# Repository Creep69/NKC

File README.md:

# NKC
## Neuauflage des NDR KLEIN COMPUTER

Hier sollen Hardware- und Softwareprojekte zum NDR Klein Computer ihren Platz finden.

Weitere Mitstreiter sind herzlich willkommen!

Links:

www.nkc-wiki.de

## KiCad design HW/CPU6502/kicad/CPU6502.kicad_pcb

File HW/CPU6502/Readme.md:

NKC CPU6502 v0.1 Prototyp 3.1.2019

Prototyp einer 65(c)02 CPU Platine für das NDR Klein Computersystem

Entwickelt von Rene Vetter mit Unterstützung von Jens Mewes basierend auf den Erläuterungen zu einer 6502-Karte am Z80-BUS:

https://ancientcomputing.blogspot.com/2017/05/a-6502-cpu-for-rc2014-part-1.html

History:

V0.1: 3.1.2019 RV
Erster Prototyp

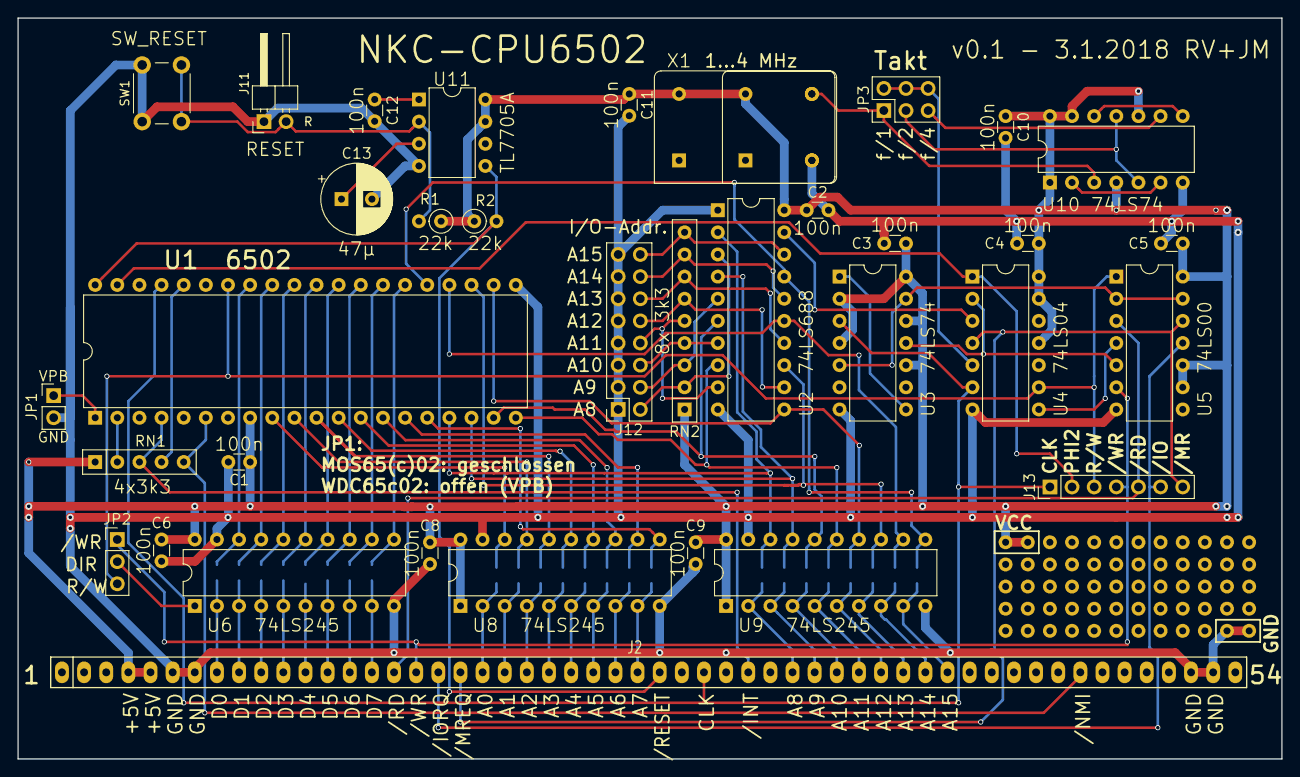
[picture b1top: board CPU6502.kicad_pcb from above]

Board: 2 copper layers, 145.0 x 85.0 mm, 39 parts (0 on the bottom side), 86 nets.

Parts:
C1, C2, C3, C4, C5, C6, C8, C9, C10, C11, C12: 100n; C_Disc_D3.0mm_W1.6mm_P2.50mm
C13: 47µ; CP_Radial_D8.0mm_P3.50mm
J2: NKC-BUS-full
J6: Conn_D; Lötbrücke_8_2
J8: Conn_A1; Lötbrücke_8_2
J9: Conn_A2; Lötbrücke_8_2
J11: RESET; PinHeader_1x02_P2.54mm_Horizontal
J12: Conn_IO_Address; PinHeader_2x08_P2.54mm_Vertical-gespiegelt
J13: Conn_Proto; PinHeader_1x07_P2.54mm_Vertical
JP1: 6502/65c02; PinHeader_1x02_P2.54mm_Vertical
JP2: /W_R/W; PinHeader_1x03_P2.54mm_Vertical
JP3: Conn_CLK; PinHeader_2x03_P2.54mm_Vertical
R1, R2: 22k; R_Axial_DIN0207_L6.3mm_D2.5mm_P2.54mm_Vertical
RN1: 4x3k3; R_Array_SIP5
RN2: 8x 3k3; R_Array_SIP9
SW1: SW_RESET; SW_PUSH_6mm
U1: 6502; DIP-40_W15.24mm
U2: 74LS688; DIP-20_W7.62mm
U3, U10: 74LS74; DIP-14_W7.62mm
U4: 74LS04; DIP-14_W7.62mm
U5: 74LS00; DIP-14_W7.62mm
U6, U8, U9: 74LS245; DIP-20_W7.62mm
U11: TL7705A; DIP-8_W7.62mm
X1: ACO-4MHz; Oscillator_DIP-14
X2: CXO_4MHz; Oscillator_DIP-8

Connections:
/-INT: J2.32, RN1.3, U1.4
/-IORQ: J2.18, J13.6, U5.11
/-MREQ: J2.19, J13.7, U4.4, U5.12
/-NMI: J2.47, RN1.5, U1.6
/-PHI2: U3.11, U4.2, U5.5
/-RD: J2.16, J13.5, U5.3
/-RESET: J2.28, R2.2, U1.40, U11.5
/-WR: J2.17, J13.4, JP2.1, U5.6
/A0: J8.1b, U1.9, U8.18
/A1: J8.2b, U1.10, U8.17
/A2: J8.3b, U1.11, U8.16
/A3: J8.4b, U1.12, U8.15
/A4: J8.5b, U1.13, U8.14
/A5: J8.6b, U1.14, U8.13
/A6: J8.7b, U1.15, U8.12
/A7: J8.8b, U1.16, U8.11
/A8: J9.1b, U1.17, U2.2, U9.18
/A9: J9.2b, U1.18, U2.4, U9.17
/A10: J9.3b, U1.19, U2.6, U9.16
/A11: J9.4b, U1.20, U2.8, U9.15
/A12: J9.5b, U1.22, U2.11, U9.14
/A13: J9.6b, U1.23, U2.13, U9.13
/A14: J9.7b, U1.24, U2.15, U9.12
/A15: J9.8b, U1.25, U2.17, U9.11
/BE: RN1.4, U1.36
/CLK: J2.30, J13.1, U1.37, U3.3, U4.6
/D0: J6.1b, U1.33, U6.18
/D1: J6.2b, U1.32, U6.17
/D2: J6.3b, U1.31, U6.16
/D3: J6.4b, U1.30, U6.15
/D4: J6.5b, U1.29, U6.14
/D5: J6.6b, U1.28, U6.13
/D6: J6.7b, U1.27, U6.12
/D7: J6.8b, U1.26, U6.11
/NKC_A0: J2.20, J8.1a, U8.2
/NKC_A1: J2.21, J8.2a, U8.3
/NKC_A2: J2.22, J8.3a, U8.4
/NKC_A3: J2.23, J8.4a, U8.5
/NKC_A4: J2.24, J8.5a, U8.6
/NKC_A5: J2.25, J8.6a, U8.7
/NKC_A6: J2.26, J8.7a, U8.8
/NKC_A7: J2.27, J8.8a, U8.9
/NKC_A8: J2.34, J9.1a, U9.2
/NKC_A9: J2.35, J9.2a, U9.3
/NKC_A10: J2.36, J9.3a, U9.4
/NKC_A11: J2.37, J9.4a, U9.5
/NKC_A12: J2.38, J9.5a, U9.6
/NKC_A13: J2.39, J9.6a, U9.7
/NKC_A14: J2.40, J9.7a, U9.8
/NKC_A15: J2.41, J9.8a, U9.9
/NKC_D0: J2.8, J6.1a, U6.2
/NKC_D1: J2.9, J6.2a, U6.3
/NKC_D2: J2.10, J6.3a, U6.4
/NKC_D3: J2.11, J6.4a, U6.5
/NKC_D4: J2.12, J6.5a, U6.6
/NKC_D5: J2.13, J6.6a, U6.7
/NKC_D6: J2.14, J6.7a, U6.8
/NKC_D7: J2.15, J6.8a, U6.9
/PHI2: J13.2, U1.39, U4.1
/R-W: J13.3, JP2.3, U1.34, U4.9, U5.1
/RDY: RN1.2, U1.2
GND: C1.2, C2.2, C3.2, C4.2, C5.2, C6.2, C8.2, C9.2, C10.2, C11.2, C12.2, C13.2, J2.6, J2.7, J2.52, J2.53, J11.1, J12.1, J12.3, J12.5, J12.7, J12.9, J12.11, J12.13, J12.15, JP1.2, SW1.1, U1.21, U2.1, U2.10, U3.7, U4.7, U5.7, U6.10, U6.19, U8.10, U8.19, U9.10, U9.19, U10.7, U11.4, X1.7, X2.4
unnamed: C12.1, U11.1
unnamed: C13.1, U11.3
unnamed: J11.2, R1.2, SW1.2, U11.2
unnamed: J12.2, RN2.2, U2.3
unnamed: J12.4, RN2.3, U2.5
unnamed: J12.6, RN2.4, U2.7
unnamed: J12.8, RN2.5, U2.9
unnamed: J12.10, RN2.6, U2.12
unnamed: J12.12, RN2.7, U2.14
unnamed: J12.14, RN2.8, U2.16
unnamed: J12.16, RN2.9, U2.18
unnamed: JP1.1, U1.1
unnamed: JP2.2, U6.1
unnamed: JP3.1, U10.3, X1.8, X2.5
unnamed: JP3.2, JP3.4, JP3.6, U4.5
unnamed: JP3.3, U10.5, U10.11
unnamed: JP3.5, U10.9
unnamed: U2.19, U4.3
unnamed: U3.1, U3.8
unnamed: U3.5, U3.13, U5.2, U5.13
unnamed: U4.8, U5.4
unnamed: U10.2, U10.6
unnamed: U10.8, U10.12
VCC: C1.1, C2.1, C3.1, C4.1, C5.1, C6.1, C8.1, C9.1, C10.1, C11.1, J2.4, J2.5, R1.1, R2.1, RN1.1, RN2.1, U1.8, U2.20, U3.2, U3.4, U3.10, U3.12, U3.14, U4.11, U4.13, U4.14, U5.9, U5.10, U5.14, U6.20, U8.1, U8.20, U9.1, U9.20, U10.1, U10.4, U10.10, U10.13, U10.14, U11.7, U11.8, X1.14, X2.8

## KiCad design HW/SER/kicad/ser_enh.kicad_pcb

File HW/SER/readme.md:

verbesserte Neuauflage der SER des NKC - serielle I/O-Platine

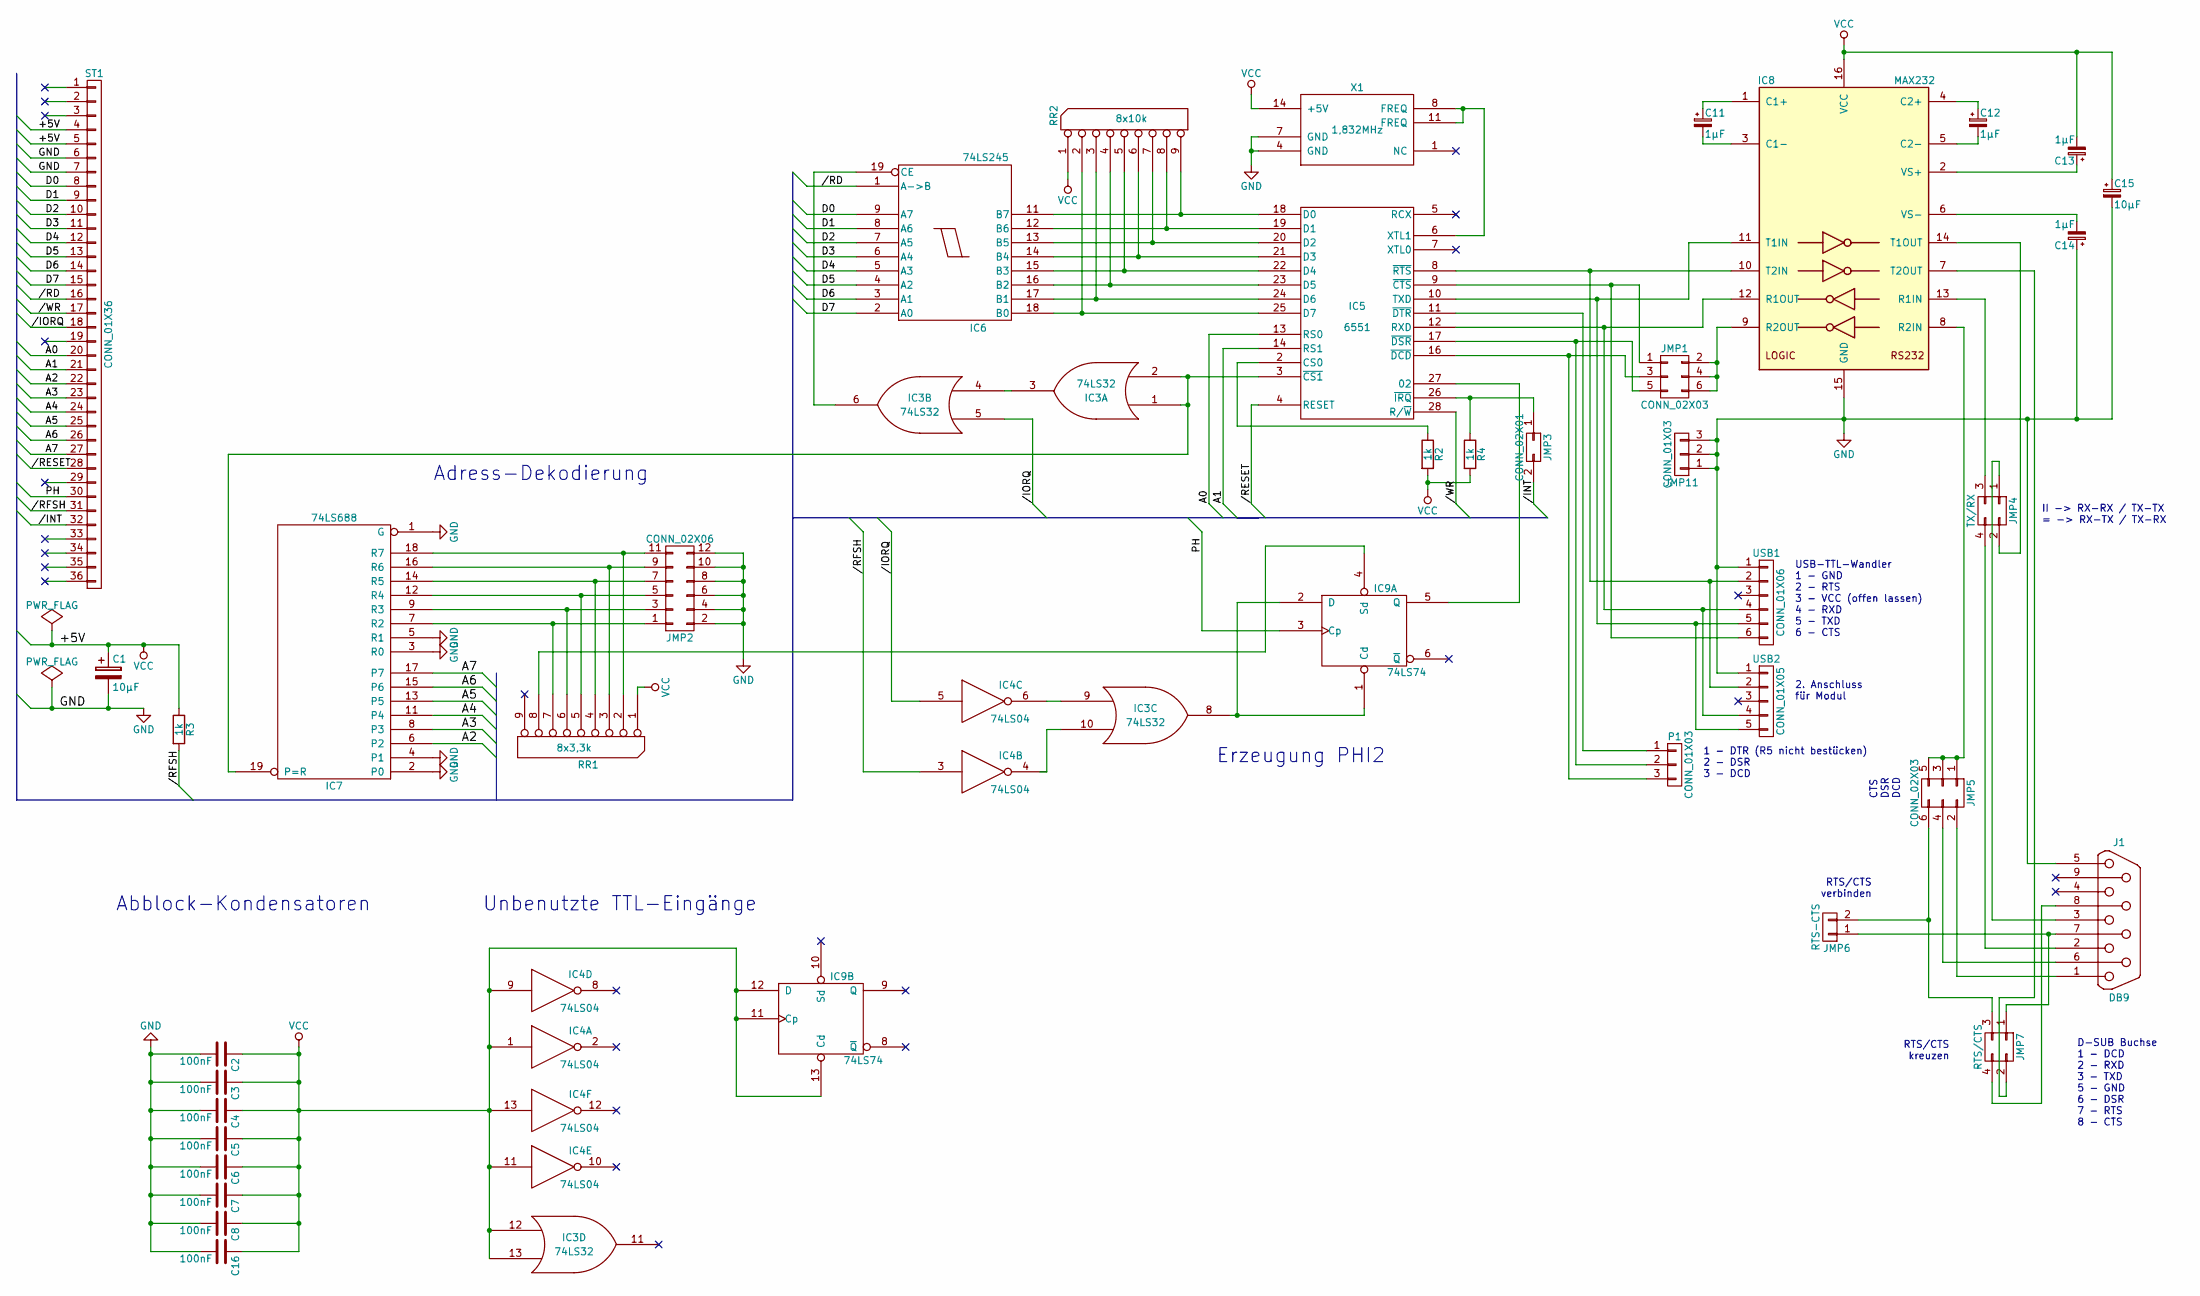
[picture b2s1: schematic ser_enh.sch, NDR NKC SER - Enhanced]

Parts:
C1: 10µF; C_Radial_D5_L6_P2.5
C2, C3, C4, C5, C6, C7, C8, C16: 100nF; C_Disc_D3_P2.5
C11, C12, C13, C14: 1µF; C_Radial_D5_L11_P2
C15: 10µF; C_Radial_D5_L11_P2
IC3: 74LS32; DIP-14
IC4: 74LS04; DIP-14
IC5: 6551; DIP-28_Breit
IC6: 74LS245; DIP-20
IC7: 74LS688; DIP-20
IC8: MAX232; DIP-16
IC9: 74LS74; DIP-14
J1: DB9; DB9MC_EU
JMP1, JMP5: CONN_02X03; Pin_Header_Straight_2x03
JMP2: CONN_02X06; Pin_Header_Straight_2x06
JMP3: CONN_02X01; Pin_Header_Straight_2x01
JMP4: TX/RX; Pin_Header_Straight_2x02
JMP6: RTS-CTS; Pin_Header_Straight_1x02
JMP7: RTS/CTS; Pin_Header_Straight_2x02
JMP11: CONN_01X03; Pin_Header_Straight_1x03
P1: CONN_01X03; Pin_Header_Straight_1x03
R2, R3, R4: 1k; Resistor_Horizontal_RM10mm
RR1: 8x3,3k; Resistor_Array_SIP8
RR2: 8x10k; Resistor_Array_SIP8
ST1: CONN_01X36; NKC_BUS_36_Names
USB1: CONN_01X06; Pin_Header_Straight_1x06
USB2: CONN_01X05; Pin_Header_Straight_1x05
X1: 1,832MHz; OSZI_6pin

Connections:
//INT: JMP3.2, ST1.32
//IORQ: IC3.5, IC4.5, ST1.18
//RD: IC6.1 (A->B), ST1.16
//RESET: IC5.4 (RESET), ST1.28
//RFSH: IC4.3, R3.2, ST1.31
//WR: IC5.28 (R/~W), ST1.17
/A0: IC5.13 (RS0), ST1.20
/A1: IC5.14 (RS1), ST1.21
/A2: IC7.6 (P2), ST1.22
/A3: IC7.8 (P3), ST1.23
/A4: IC7.11 (P4), ST1.24
/A5: IC7.13 (P5), ST1.25
/A6: IC7.15 (P6), ST1.26
/A7: IC7.17 (P7), ST1.27
/D0: IC6.9 (A7), ST1.8
/D1: IC6.8 (A6), ST1.9
/D2: IC6.7 (A5), ST1.10
/D3: IC6.6 (A4), ST1.11
/D4: IC6.5 (A3), ST1.12
/D5: IC6.4 (A2), ST1.13
/D6: IC6.3 (A1), ST1.14
/D7: IC6.2 (A0), ST1.15
/PH: IC9.3 (Cp), ST1.30
GND: C1.2, C2.2, C3.2, C4.2, C5.2, C6.2, C7.2, C8.2, C14.1, C15.2, C16.2, IC3.7 (GND), IC4.7 (GND), IC5.1 (GND), IC6.10 (GND), IC7.1 (G), IC7.2 (P0), IC7.3 (R0), IC7.4 (P1), IC7.5 (R1), IC7.10 (GND), IC8.15 (GND), IC9.7 (GND), J1.5, JMP2.2, JMP2.4, JMP2.6, JMP2.8, JMP2.10, JMP2.12, JMP11.1, JMP11.2, JMP11.3, ST1.6, ST1.7, USB1.1, USB2.1, X1.4 (GND), X1.7 (GND)
unnamed: C11.1, IC8.1 (C1+)
unnamed: C11.2, IC8.3 (C1-)
unnamed: C12.1, IC8.4 (C2+)
unnamed: C12.2, IC8.5 (C2-)
unnamed: C13.1, IC8.2 (VS+)
unnamed: C14.2, IC8.6 (VS-)
unnamed: IC3.1, IC3.2, IC5.3 (~CS1), IC7.19 (P=R)
unnamed: IC3.3, IC3.4
unnamed: IC3.6, IC6.19 (CE)
unnamed: IC3.8, IC9.1 (Cd), IC9.2 (D)
unnamed: IC3.9, IC4.6
unnamed: IC3.10, IC4.4
unnamed: IC5.2 (CS0), R2.1
unnamed: IC5.6 (XTL1), X1.8 (FREQ), X1.11 (FREQ)
unnamed: IC5.8 (~RTS), IC8.10 (T2IN), USB1.2, USB2.2
unnamed: IC5.9 (~CTS), JMP1.1, USB1.6
unnamed: IC5.10 (TXD), IC8.11 (T1IN), USB1.5, USB2.5
unnamed 41: IC5.11 (~DTR), P1.1; also elsewhere on the board
unnamed: IC5.12 (RXD), IC8.12 (R1OUT), USB1.4, USB2.4
unnamed: IC5.16 (~DCD), JMP1.3, P1.3
unnamed: IC5.17 (~DSR), JMP1.5, P1.2
unnamed: IC5.18 (D0), IC6.11 (B7), RR2.9
unnamed: IC5.19 (D1), IC6.12 (B6), RR2.8
unnamed: IC5.20 (D2), IC6.13 (B5), RR2.7
unnamed: IC5.21 (D3), IC6.14 (B4), RR2.6
unnamed: IC5.22 (D4), IC6.15 (B3), RR2.5
unnamed: IC5.23 (D5), IC6.16 (B2), RR2.4
unnamed: IC5.24 (D6), IC6.17 (B1), RR2.3
unnamed: IC5.25 (D7), IC6.18 (B0), RR2.2
unnamed: IC5.26 (~IRQ), JMP3.1, R4.1
unnamed: IC5.27 (02), IC9.5 (Q)
unnamed: IC7.7 (R2), JMP2.1, RR1.7
unnamed: IC7.9 (R3), JMP2.3, RR1.6
unnamed: IC7.12 (R4), JMP2.5, RR1.5
unnamed: IC7.14 (R5), JMP2.7, RR1.4
unnamed: IC7.16 (R6), JMP2.9, RR1.3
unnamed: IC7.18 (R7), JMP2.11, RR1.2
unnamed: IC8.7 (T2OUT), JMP7.2
unnamed: IC8.8 (R2IN), JMP5.1, JMP5.3, JMP5.5
unnamed: IC8.9 (R2OUT), JMP1.2, JMP1.4, JMP1.6
unnamed: IC8.13 (R1IN), JMP4.3
unnamed: IC8.14 (T1OUT), JMP4.2
unnamed: IC9.4 (Sd), RR1.8
unnamed: J1.1, JMP5.2
unnamed: J1.2, JMP4.4
unnamed: J1.3, JMP4.1
unnamed: J1.6, JMP5.4
unnamed: J1.7, JMP6.1, JMP7.1
unnamed: J1.8, JMP7.4
unnamed: JMP5.6, JMP6.2, JMP7.3
VCC: C1.1, C2.1, C3.1, C4.1, C5.1, C6.1, C7.1, C8.1, C13.2, C15.1, C16.1, IC3.12, IC3.13, IC3.14 (VCC), IC4.1, IC4.9, IC4.11, IC4.13, IC4.14 (VCC), IC5.15 (Vcc), IC6.20 (VCC), IC7.20 (VCC), IC8.16 (VCC), IC9.11 (Cp), IC9.12 (D), IC9.13 (Cd), IC9.14 (VCC), R2.2, R3.1, R4.2, RR1.1 (COM), RR2.1 (COM), ST1.4, ST1.5, X1.14 (+5V); also elsewhere on the board

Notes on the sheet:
D-SUB Buchse 1 - DCD 2 - RXD 3 - TXD 5 - GND 6 - DSR 7 - RTS 8 - CTS
USB-TTL-Wandler 1 - GND 2 - RTS 3 - VCC (offen lassen) 4 - RXD 5 - TXD 6 - CTS
1 - DTR (R5 nicht bestücken) 2 - DSR 3 - DCD
Adress-Dekodierung
Erzeugung PHI2
Abblock-Kondensatoren
Unbenutzte TTL-Eingänge
II -> RX-RX / TX-TX = -> RX-TX / TX-RX
CTS DSR DCD
2. Anschluss für Modul
RTS/CTS verbinden
RTS/CTS kreuzen

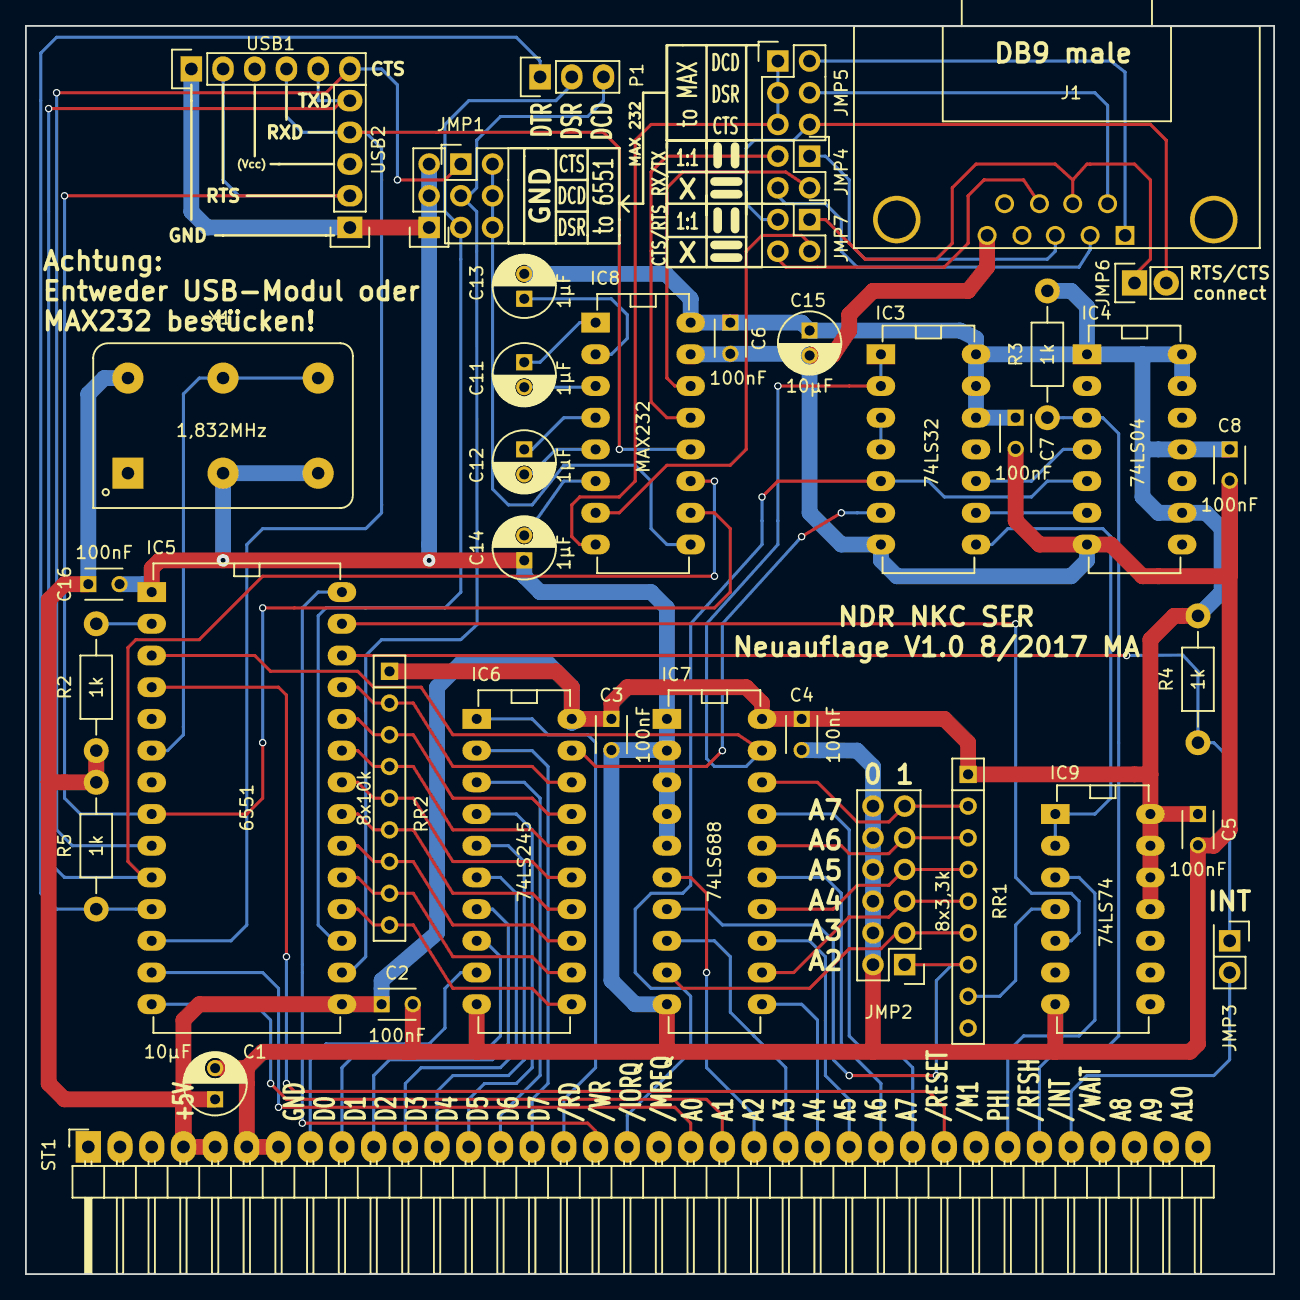
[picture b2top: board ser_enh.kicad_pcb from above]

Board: 2 copper layers, 100.0 x 100.0 mm, 41 parts (0 on the bottom side), 75 nets.

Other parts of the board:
R5: 1k; Resistor_Horizontal_RM10mm

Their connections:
unnamed 41: R5.1; also elsewhere on the board
VCC: R5.2; also elsewhere on the board

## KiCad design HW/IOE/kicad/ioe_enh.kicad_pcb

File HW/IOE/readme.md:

verbesserte Neuauflage der IOE des NKC - parallele I/O-Platine

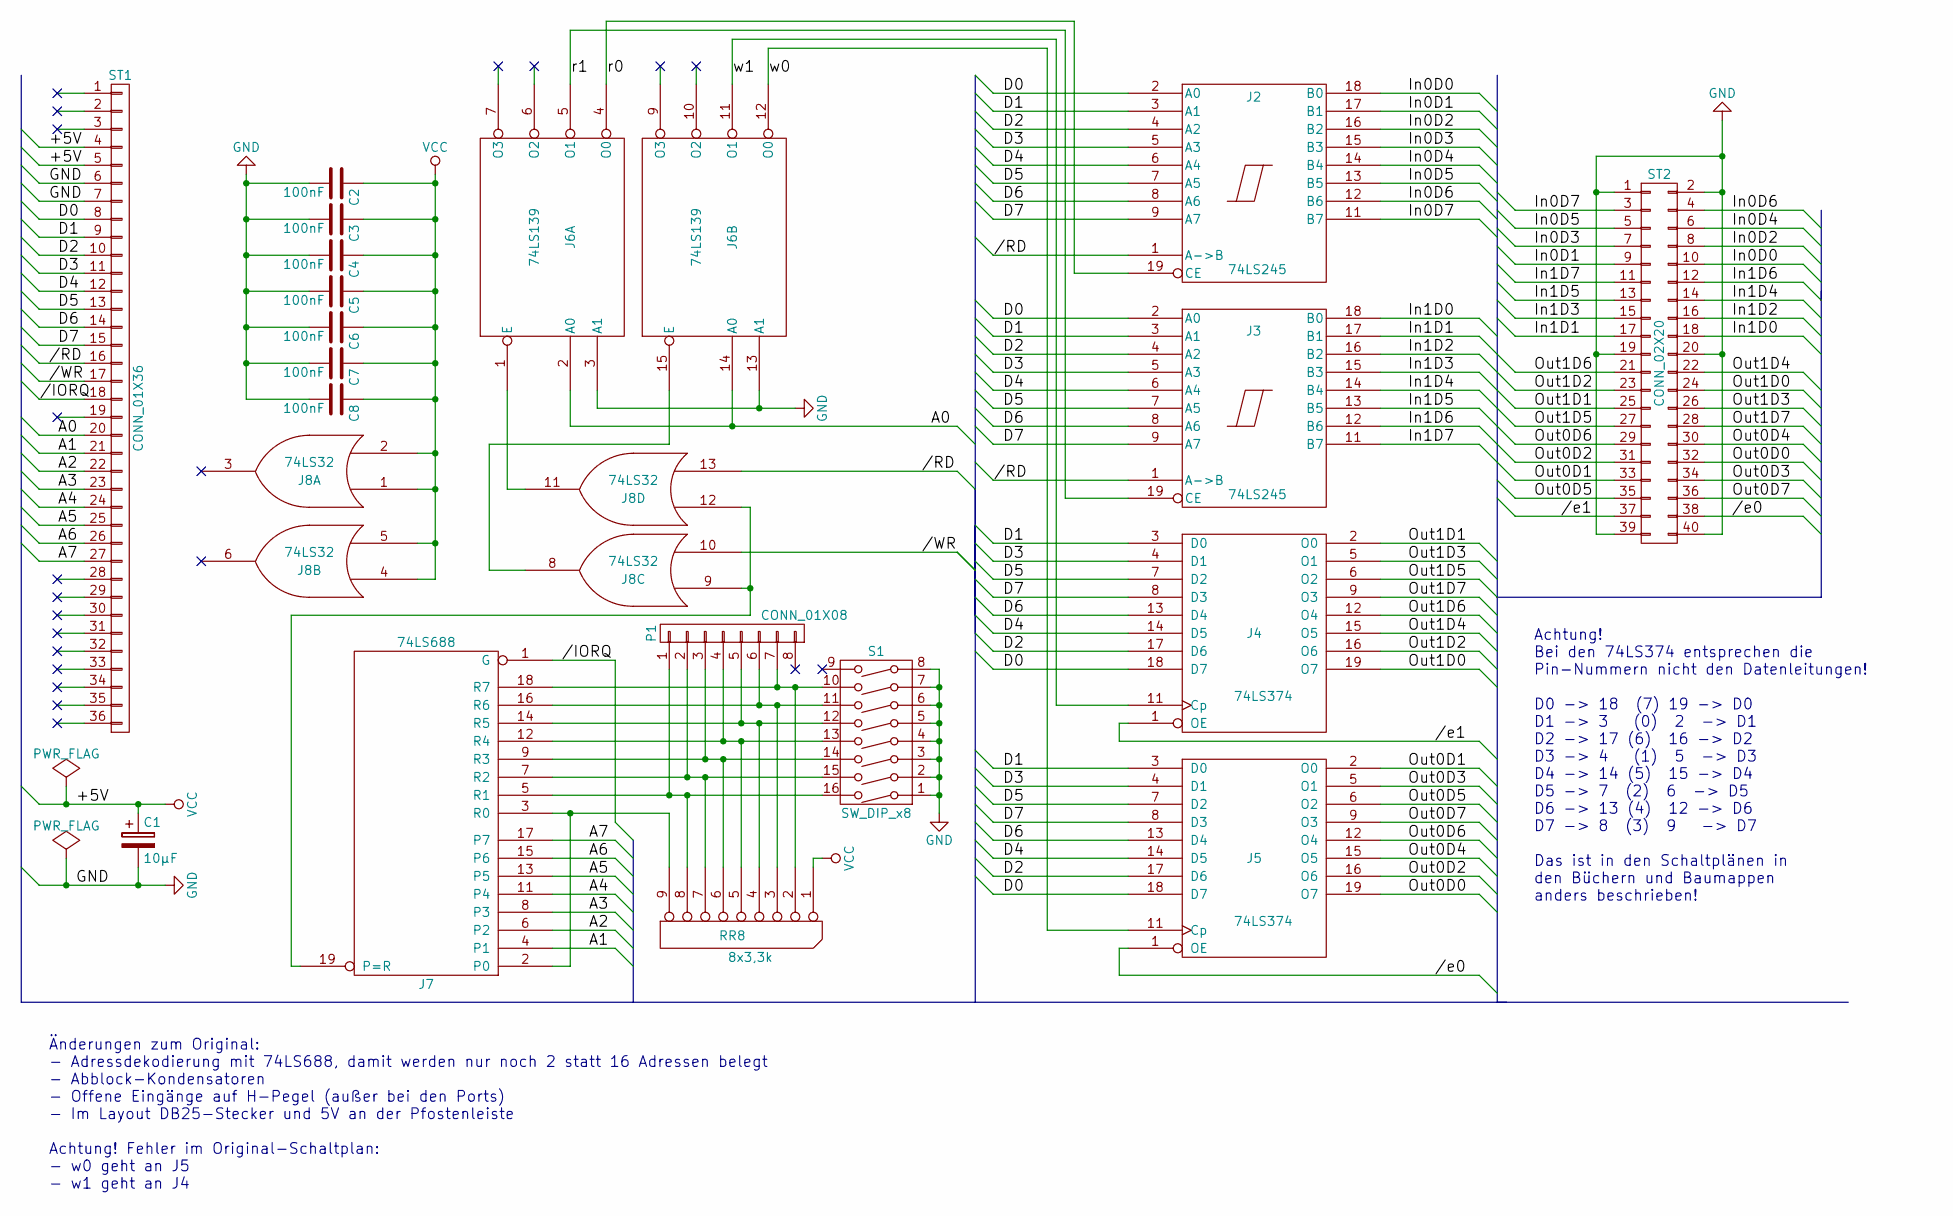
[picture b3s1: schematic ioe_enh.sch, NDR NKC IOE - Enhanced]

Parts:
8x3,3k: RR8; Resistor_Array_SIP8
C1: 10µF; C_Radial_D5_L6_P2.5
C2, C3, C4, C5, C6, C7, C8: 100nF; C_Disc_D3_P2.5
J2, J3: 74LS245; DIP-20_W7.62mm_LongPads
J4, J5: 74LS374; DIP-20_W7.62mm_LongPads
J6: 74LS139; DIP-16_W7.62mm_LongPads
J7: 74LS688; DIP-20_W7.62mm_LongPads
J8: 74LS32; DIP-14_W7.62mm_LongPads
P1: CONN_01X08; Pin_Header_Straight_1x08
S1: SW_DIP_x8; DIP-16_W7.62mm_LongPads
ST1: CONN_01X36; NKC_BUS_36
ST2: CONN_02X20; Pin_Header_Straight_2x20

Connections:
//IORQ: J7.1 (G), ST1.18
//RD: J2.1 (A->B), J3.1 (A->B), J8.13, ST1.16
//WR: J8.10, ST1.17
//e0: J5.1 (OE), ST2.38
//e1: J4.1 (OE), ST2.37
/A0: J6.2 (A0), J6.14 (A0), ST1.20
/A1: J7.4 (P1), ST1.21
/A2: J7.6 (P2), ST1.22
/A3: J7.8 (P3), ST1.23
/A4: J7.11 (P4), ST1.24
/A5: J7.13 (P5), ST1.25
/A6: J7.15 (P6), ST1.26
/A7: J7.17 (P7), ST1.27
/D0: J2.2 (A0), J3.2 (A0), J4.18 (D7), J5.18 (D7), ST1.8
/D1: J2.3 (A1), J3.3 (A1), J4.3 (D0), J5.3 (D0), ST1.9
/D2: J2.4 (A2), J3.4 (A2), J4.17 (D6), J5.17 (D6), ST1.10
/D3: J2.5 (A3), J3.5 (A3), J4.4 (D1), J5.4 (D1), ST1.11
/D4: J2.6 (A4), J3.6 (A4), J4.14 (D5), J5.14 (D5), ST1.12
/D5: J2.7 (A5), J3.7 (A5), J4.7 (D2), J5.7 (D2), ST1.13
/D6: J2.8 (A6), J3.8 (A6), J4.13 (D4), J5.13 (D4), ST1.14
/D7: J2.9 (A7), J3.9 (A7), J4.8 (D3), J5.8 (D3), ST1.15
/In0D0: J2.18 (B0), ST2.10
/In0D1: J2.17 (B1), ST2.9
/In0D2: J2.16 (B2), ST2.8
/In0D3: J2.15 (B3), ST2.7
/In0D4: J2.14 (B4), ST2.6
/In0D5: J2.13 (B5), ST2.5
/In0D6: J2.12 (B6), ST2.4
/In0D7: J2.11 (B7), ST2.3
/In1D0: J3.18 (B0), ST2.18
/In1D1: J3.17 (B1), ST2.17
/In1D2: J3.16 (B2), ST2.16
/In1D3: J3.15 (B3), ST2.15
/In1D4: J3.14 (B4), ST2.14
/In1D5: J3.13 (B5), ST2.13
/In1D6: J3.12 (B6), ST2.12
/In1D7: J3.11 (B7), ST2.11
/Out0D0: J5.19 (O7), ST2.32
/Out0D1: J5.2 (O0), ST2.33
/Out0D2: J5.16 (O6), ST2.31
/Out0D3: J5.5 (O1), ST2.34
/Out0D4: J5.15 (O5), ST2.30
/Out0D5: J5.6 (O2), ST2.35
/Out0D6: J5.12 (O4), ST2.29
/Out0D7: J5.9 (O3), ST2.36
/Out1D0: J4.19 (O7), ST2.24
/Out1D1: J4.2 (O0), ST2.25
/Out1D2: J4.16 (O6), ST2.23
/Out1D3: J4.5 (O1), ST2.26
/Out1D4: J4.15 (O5), ST2.22
/Out1D5: J4.6 (O2), ST2.27
/Out1D6: J4.12 (O4), ST2.21
/Out1D7: J4.9 (O3), ST2.28
/r0: J2.19 (CE), J6.4 (O0)
/r1: J3.19 (CE), J6.5 (O1)
/w0: J5.11 (Cp), J6.12 (O0)
/w1: J4.11 (Cp), J6.11 (O1)
GND: C1.2, C2.2, C3.2, C4.2, C5.2, C6.2, C7.2, C8.2, J2.10 (GND), J3.10 (GND), J4.10 (GND), J5.10 (GND), J6.3 (A1), J6.8 (GND), J6.13 (A1), J7.10 (GND), J8.7 (GND), S1.1, S1.2, S1.3, S1.4, S1.5, S1.6, S1.7, S1.8, ST1.6, ST1.7, ST2.1, ST2.2, ST2.19, ST2.20, ST2.39, ST2.40
unnamed: 8x3,3k.2, J7.18 (R7), P1.7, S1.10
unnamed: 8x3,3k.3, J7.16 (R6), P1.6, S1.11
unnamed: 8x3,3k.4, J7.14 (R5), P1.5, S1.12
unnamed: 8x3,3k.5, J7.12 (R4), P1.4, S1.13
unnamed: 8x3,3k.6, J7.9 (R3), P1.3, S1.14
unnamed: 8x3,3k.7, J7.7 (R2), P1.2, S1.15
unnamed: 8x3,3k.8, J7.5 (R1), P1.1, S1.16
unnamed: 8x3,3k.9, J7.2 (P0), J7.3 (R0)
unnamed: J6.1 (E), J8.11
unnamed: J6.15 (E), J8.8
unnamed: J7.19 (P=R), J8.9, J8.12
VCC: 8x3,3k.1 (COM), C1.1, C2.1, C3.1, C4.1, C5.1, C6.1, C7.1, C8.1, J2.20 (VCC), J3.20 (VCC), J4.20 (VCC), J5.20 (VCC), J6.16 (VCC), J7.20 (VCC), J8.1, J8.2, J8.4, J8.5, J8.14 (VCC), ST1.4, ST1.5

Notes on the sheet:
Achtung! Bei den 74LS374 entsprechen die Pin-Nummern nicht den Datenleitungen! D0 -> 18 (7) 19 -> D0 D1 -> 3 (0) 2 -> D1 D2 -> 17 (6) 16 -> D2 D3 -> 4 (1) 5 -> D3 D4 -> 14 (5) 15 -> D4 D5 -> 7 (2) 6 -> D5 D6 -> 13 (4) 12 -> D6 D7 -> 8 (3) 9 -> D7 Das ist in den Schaltplänen in den Büchern und Bauma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
Änderungen zum Original: - Adressdekodierung mit 74LS688, damit werden nur noch 2 statt 16 Adressen belegt - Abblock-Kondensatoren - Offene Eingänge auf H-Pegel (außer bei den Ports) - Im Layout DB25-Stecker und 5V an der Pfostenleiste Achtung! Fehler im Original-Schaltplan: - w0 geht an J5 - w1 ge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

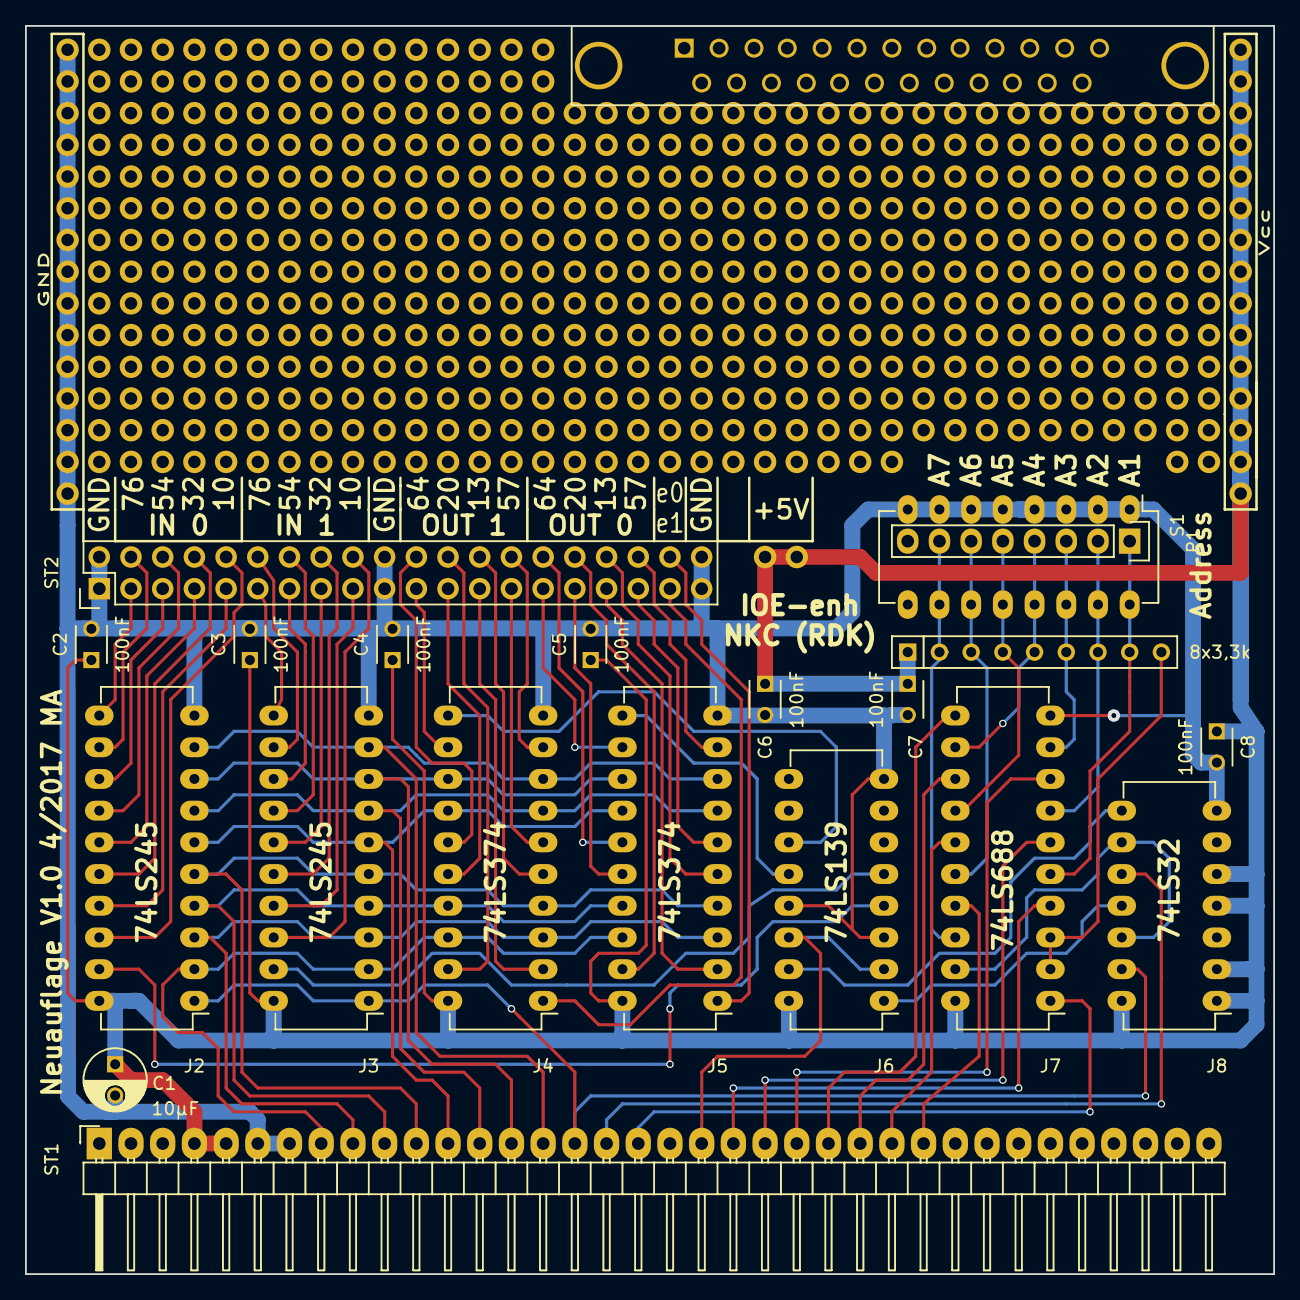
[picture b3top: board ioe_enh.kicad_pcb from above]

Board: 2 copper layers, 100.0 x 100.0 mm, 20 parts (0 on the bottom side), 70 nets.

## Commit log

2017-10-20 Create NKC-BUS2
2017-10-20 Create sprint_layout_6
2017-10-20 Version v1.2 und v1.2 der BUS2 Platine für Sprint Layout 6
2017-10-20 Gerber Files der v1.2 der BUS2 Platine Passend für z.B. Elecrow und DirtyPCB
2017-10-20 change in structure
2017-10-20 initial
2017-10-20 initial release
2017-10-20 initial version
2017-12-03 Dokumentation für CSP Platine
2018-02-04 Dokumentation zur IO-USB
2019-01-03 Version 0.1 Prototyp
2019-01-26 Zusätzliche Verbindung für Tastaturpuffer.
2021-06-12 initial version of python_dl
2021-06-13 added Macro for SER Overflow check
2021-06-13 added DS utility
2021-06-13 added readme
2021-06-15 update and cleanup
2021-06-15 initial version of xtree
2021-06-15 Small update
2021-06-15 Minor update
2021-06-16 initial version of XDIR
2021-06-16 move files to 68k folder
2021-06-16 update Python to take care on file end of ascii files
2021-06-16 initial version of color-mandelbrot
2021-06-19 Unterverzeichnisse fuer Programmiersprachen Erstes "Hello World" Programm in C
2021-06-19 erste Routinen zur Nutzung der CAS-neo in C Programmen
2021-06-19 minor cleanup
2021-06-19 Update typo
2021-06-30 Bugfix for HDD's
2021-07-01 bugfix for HDD's and copy command
2021-07-05 added xt.68k
2021-07-11 bugfix for send_file
2021-07-18 Erster Testcode fuer NKC-LCD
2021-07-20 added executable for 68008 and 68000
2021-07-27 Added 68k exe for 68008 + 68000
2021-07-30 small bugfix
2021-08-04 Testroutine fuer SOUND3 auf 0x50
2021-08-30 Update - added 115200 Baud for GDP-FPGA
2021-10-16 add CPU68k8 layout files
2021-10-16 add CPU68k16 layout files
2021-10-16 add BANKBOOT2 layout files
2021-10-16 add BWS layout files
2021-10-16 add CPU8080 layout files
2021-10-16 add GDP64HS layout files
2021-10-16 add updated NKC-LCD gerber files
2021-10-16 add updated SOUND3 layout files
2021-10-16 add updated SIO-CTC-PIO layout files
2022-09-24 initial Version of Tetris Game for NKC
2022-09-29 Update for tetris
2022-10-09 update - Save of Highscore
2022-10-10 bugfix for highscore list and stone rotation
2023-01-07 minor bugfix
2023-01-17 new version now with beginner and intermediate (commandline parameter: -i) mode and 3D effects
2023-10-22 added mine_m (S/W output) for regular GDP64-HS
2023-10-22 Added keyboard mode
2023-10-29 update for S/W Version of Minesweeper - stores now also highscore to file. May be displayed when started with -h Parameter
2023-10-30 update added explosion sound
2023-10-31 bugfix
2024-03-29 Update sysinfo.asm
    Ein paar Zeilen, um beim SCSI-Laufwerk Namen und Modell anzuzeigen statt nur "vorhanden". GitHub will leider immer die Umlaute in UTF-8 ändern, müssen wir mal sehen, ob das klappt.
2024-04-05 Update sysinfo.asm
    Wert von gets2i in D2 statt D1 retten, da der folgende SCSI-Befehl D1 überschreibt.
2025-10-15 Ansicht der BUS2
    BUS2 Neuauflage 26.4.2017 v1.2 RV mit Platinenhalterung und 5V Anschlusskabel via Anderson Powerpoles
2025-10-15 Create 20251014_BUS2.txt
    Kurze Beschreibung zur Konfektionierung der BUS2
2025-10-15 STL Datei für Platinenhalter zu BUS2
    STL Datei zum Ausdruck des Platinenhalters für die NKC BUS2 (Neuauflage 26.4.2017 v 1.2 RV) auf dem 3D-Drucker
2025-10-20 Readme.md
2025-10-21 Update Info zur BUs2
2025-10-21 Datei umbenannt
2025-10-21 Bauinformation
